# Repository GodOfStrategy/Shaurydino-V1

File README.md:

# Shaurdino-V1
A custom devboard tailored for small and medium applications.
I plan to use it to efficiently reduce electricity consumption in a voice recorder and announcer module of my own.

Key Features
Core MCU:

Raspberry Pi RP2040 dual‑core ARM Cortex‑M0+ processor.

Connected to a 12 MHz crystal oscillator for precise clocking.

USB Interface:

USB‑C connector with ESD protection (USBLC6‑2SC6).

NCP-1117 linear voltage regulator providing a clean 3.3 V rail.

Decoupling capacitors distributed across the board for stable supply.

Designed to accept 5 V from USB or a regulated external source.

Memory:

W25Q32JVSS QSPI flash for program and data storage.

Connected via dedicated QSPI pins for high‑speed access.

Connectivity & Expansion:

Dual 20‑pin headers, exposing GPIO0–GPIO29, ADC inputs, and power rails for running peripherals safely.

Breakout for SWCLK and SWDIO debug signals.

RUN pin with pull‑up for reset control.

Supporting Components:

Crystal oscillator network with capacitors and resistor for stable timing.

Multiple capacitors (C1–C17, C36–C39) for filtering and decoupling higher frequency  and low frequency smoothning.

Resistors for pull‑ups/pull‑downs and configuring certain components.

Here is the 3D model of my PCB.

You can find the schematics in the repository as well as the PCB design and it's Gerber files.
Here are the PCB and Schematics Images for your reference here aswell:

The BOM for the project-

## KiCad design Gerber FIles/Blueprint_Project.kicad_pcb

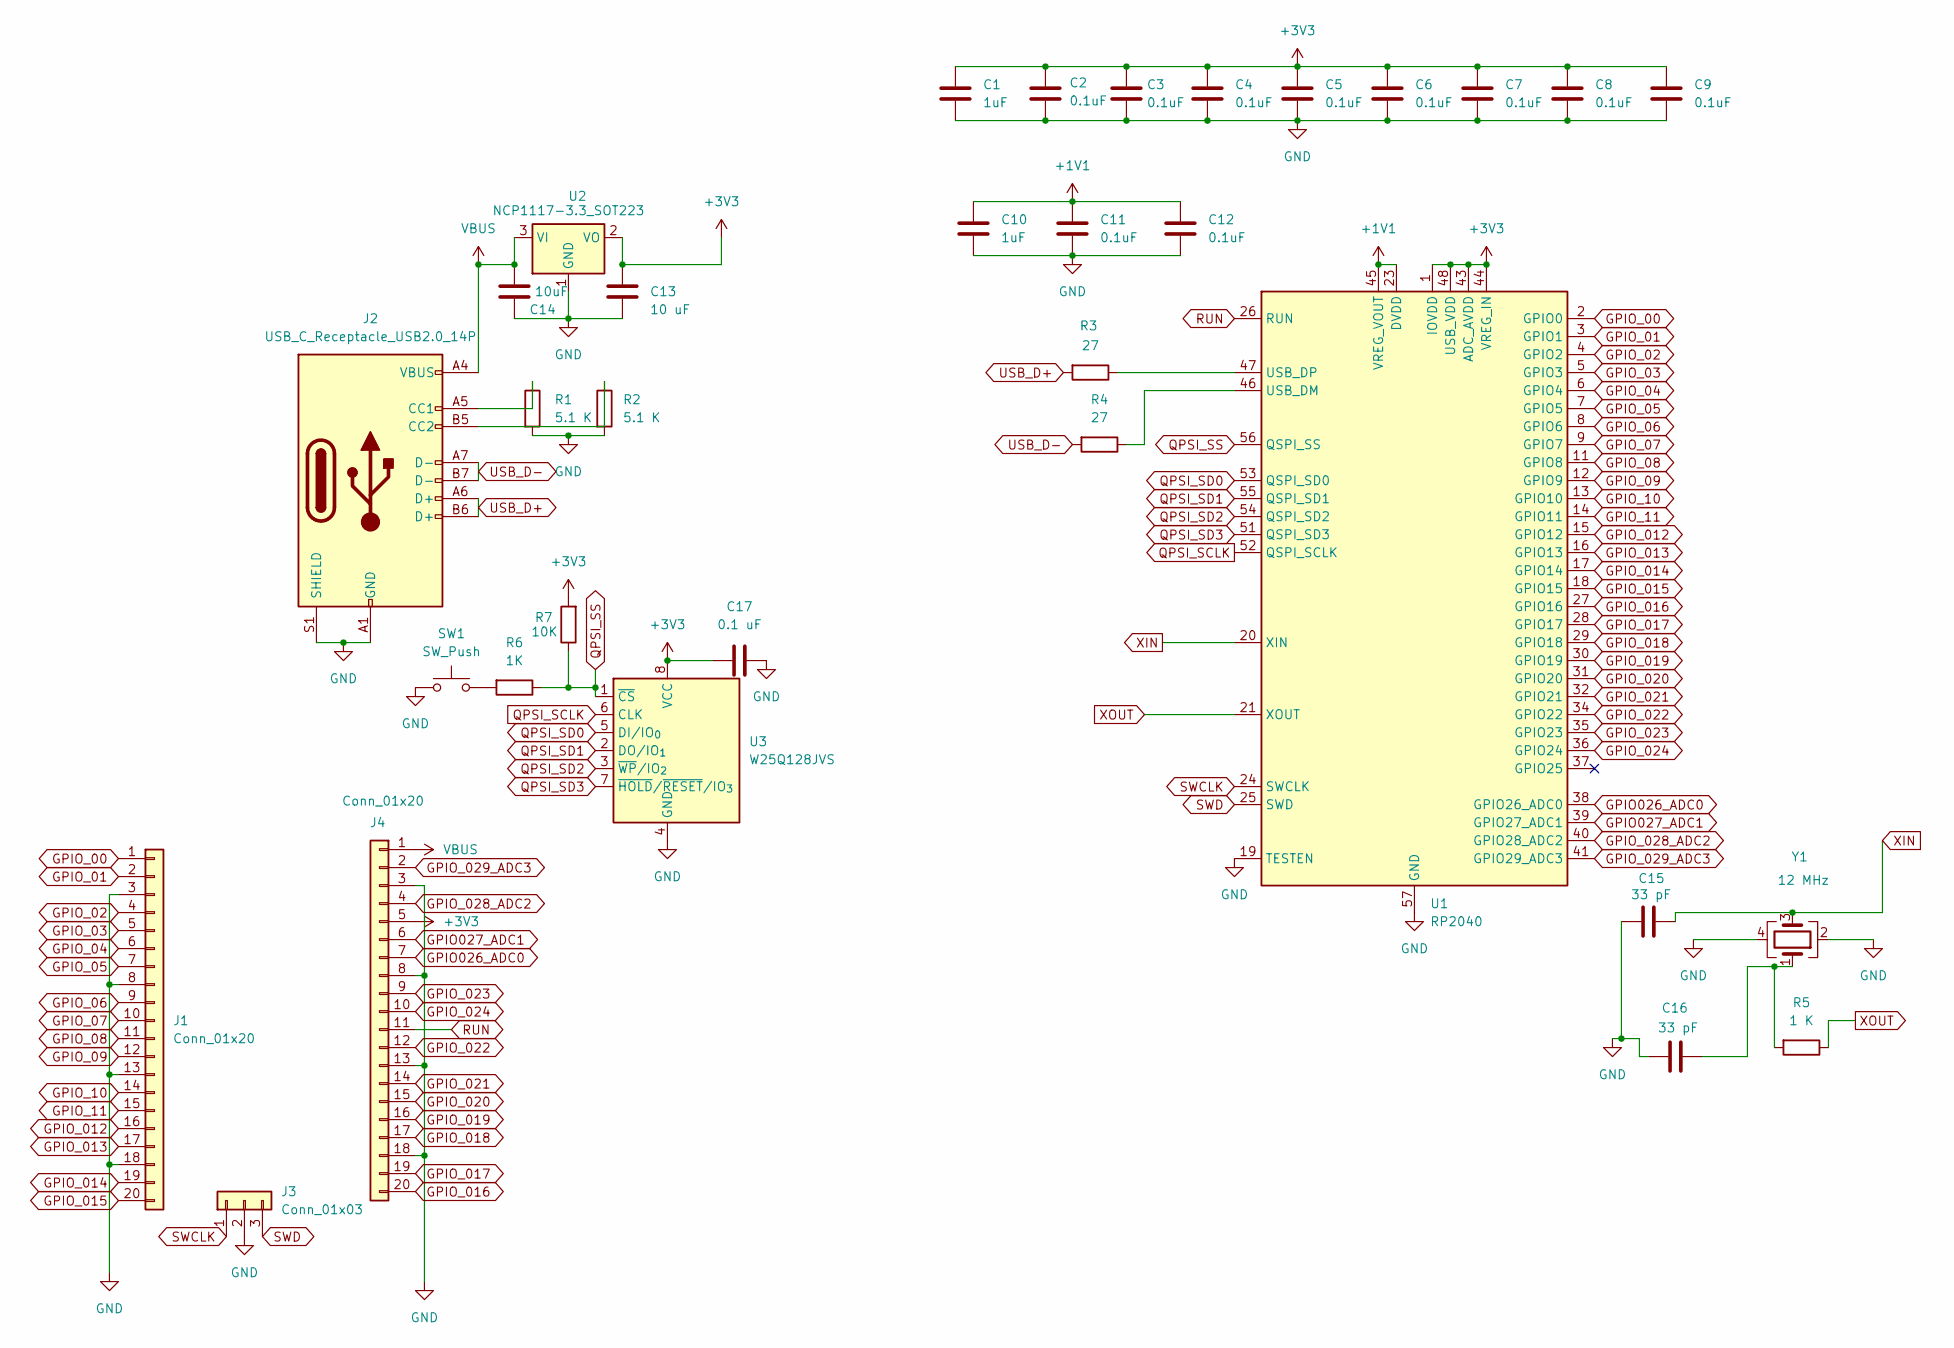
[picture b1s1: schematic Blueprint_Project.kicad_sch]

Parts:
C1, C10: 1uF; C_0402_1005Metric
C2, C3, C4, C5, C6, C7, C8, C9, C11, C12: 0.1uF; C_0402_1005Metric
C13: 10 uF; C_0201_0603Metric
C14: 10uF; C_0201_0603Metric
C15, C16: 33 pF; C_0402_1005Metric
C17: 0.1 uF; C_0402_1005Metric
J1, J4: Conn_01x20; PinHeader_1x20_P2.54mm_Vertical
J2: USB_C_Receptacle_USB2.0_14P; USB_C_Receptacle_HRO_TYPE-C-31-M-12
J3: Conn_01x03; PinHeader_1x03_P2.54mm_Vertical
R1, R2: 5.1 K; R_0402_1005Metric
R3, R4: 27; R_0402_1005Metric
R5: 1 K; R_0402_1005Metric
R6: 1K; R_0402_1005Metric
R7: 10K; R_0402_1005Metric
SW1: SW_Push; SW_Push_SPST_NO_Alps_SKRK
U1: RP2040; QFN-56-1EP_7x7mm_P0.4mm_EP3.2x3.2mm
U2: NCP1117-3.3_SOT223; SOT-223-3_TabPin2
U3: W25Q128JVS; SOIC-8_5.3x5.3mm_P1.27mm
Y1: 12 MHz; Crystal_SMD_3225-4Pin_3.2x2.5mm

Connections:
+1V1: C10.1, C11.1, C12.1, U1.23 (DVDD), U1.45 (VREG_VOUT), U1.50 (DVDD)
+3V3: C1.1, C2.1, C3.1, C4.1, C5.1, C6.1, C7.1, C8.1, C9.1, C13.1, C17.2, J4.5, R7.2, U1.1 (IOVDD), U1.10 (IOVDD), U1.22 (IOVDD), U1.33 (IOVDD), U1.42 (IOVDD), U1.43 (ADC_AVDD), U1.44 (VREG_IN), U1.48 (USB_VDD), U1.49 (IOVDD), U2.2 (VO), U3.8 (VCC)
GND: C1.2, C2.2, C3.2, C4.2, C5.2, C6.2, C7.2, C8.2, C9.2, C10.2, C11.2, C12.2, C13.2, C14.2, C15.2, C16.2, C17.1, J1.3, J1.8, J1.13, J1.18, J2.A1 (GND), J2.A12 (GND), J2.B1 (GND), J2.B12 (GND), J2.S1 (SHIELD), J3.2, J4.3, J4.8, J4.13, J4.18, R1.2, R2.2, SW1.1, U1.19 (TESTEN), U1.57 (GND), U2.1 (GND), U3.4 (GND), Y1.2, Y1.4
GPIO026_ADC0: J4.7, U1.38 (GPIO26_ADC0)
GPIO027_ADC1: J4.6, U1.39 (GPIO27_ADC1)
GPIO_00: J1.1, U1.2 (GPIO0)
GPIO_01: J1.2, U1.3 (GPIO1)
GPIO_02: J1.4, U1.4 (GPIO2)
GPIO_03: J1.5, U1.5 (GPIO3)
GPIO_04: J1.6, U1.6 (GPIO4)
GPIO_05: J1.7, U1.7 (GPIO5)
GPIO_06: J1.9, U1.8 (GPIO6)
GPIO_07: J1.10, U1.9 (GPIO7)
GPIO_08: J1.11, U1.11 (GPIO8)
GPIO_09: J1.12, U1.12 (GPIO9)
GPIO_10: J1.14, U1.13 (GPIO10)
GPIO_11: J1.15, U1.14 (GPIO11)
GPIO_012: J1.16, U1.15 (GPIO12)
GPIO_013: J1.17, U1.16 (GPIO13)
GPIO_014: J1.19, U1.17 (GPIO14)
GPIO_015: J1.20, U1.18 (GPIO15)
GPIO_016: J4.20, U1.27 (GPIO16)
GPIO_017: J4.19, U1.28 (GPIO17)
GPIO_018: J4.17, U1.29 (GPIO18)
GPIO_019: J4.16, U1.30 (GPIO19)
GPIO_020: J4.15, U1.31 (GPIO20)
GPIO_021: J4.14, U1.32 (GPIO21)
GPIO_022: J4.12, U1.34 (GPIO22)
GPIO_023: J4.9, U1.35 (GPIO23)
GPIO_024: J4.10, U1.36 (GPIO24)
GPIO_028_ADC2: J4.4, U1.40 (GPIO28_ADC2)
GPIO_029_ADC3: J4.2, U1.41 (GPIO29_ADC3)
unnamed: C16.1, R5.2, Y1.1
unnamed: J2.A5 (CC1), R1.1
unnamed: J2.B5 (CC2), R2.1
unnamed: R6.2, SW1.2
unnamed: R4.1, U1.46 (USB_DM)
unnamed: R3.1, U1.47 (USB_DP)
QPSI_SCLK: U1.52 (QSPI_SCLK), U3.6 (CLK)
QPSI_SD0: U1.53 (QSPI_SD0), U3.5 (DI/IO_{0})
QPSI_SD1: U1.55 (QSPI_SD1), U3.2 (DO/IO_{1})
QPSI_SD2: U1.54 (QSPI_SD2), U3.3 (~WP/IO_{2})
QPSI_SD3: U1.51 (QSPI_SD3), U3.7 (~HOLD/~RESET/IO_{3})
QPSI_SS: R6.1, R7.1, U1.56 (QSPI_SS), U3.1 (~CS)
RUN: J4.11, U1.26 (RUN)
SWCLK: J3.1, U1.24 (SWCLK)
SWD: J3.3, U1.25 (SWD)
USB_D+: J2.A6 (D+), J2.B6 (D+), R3.2
USB_D-: J2.A7 (D-), J2.B7 (D-), R4.2
VBUS: C14.1, J2.A4 (VBUS), J2.A9 (VBUS), J2.B4 (VBUS), J2.B9 (VBUS), J4.1, U2.3 (VI)
XIN: C15.1, U1.20 (XIN), Y1.3
XOUT: R5.1, U1.21 (XOUT)

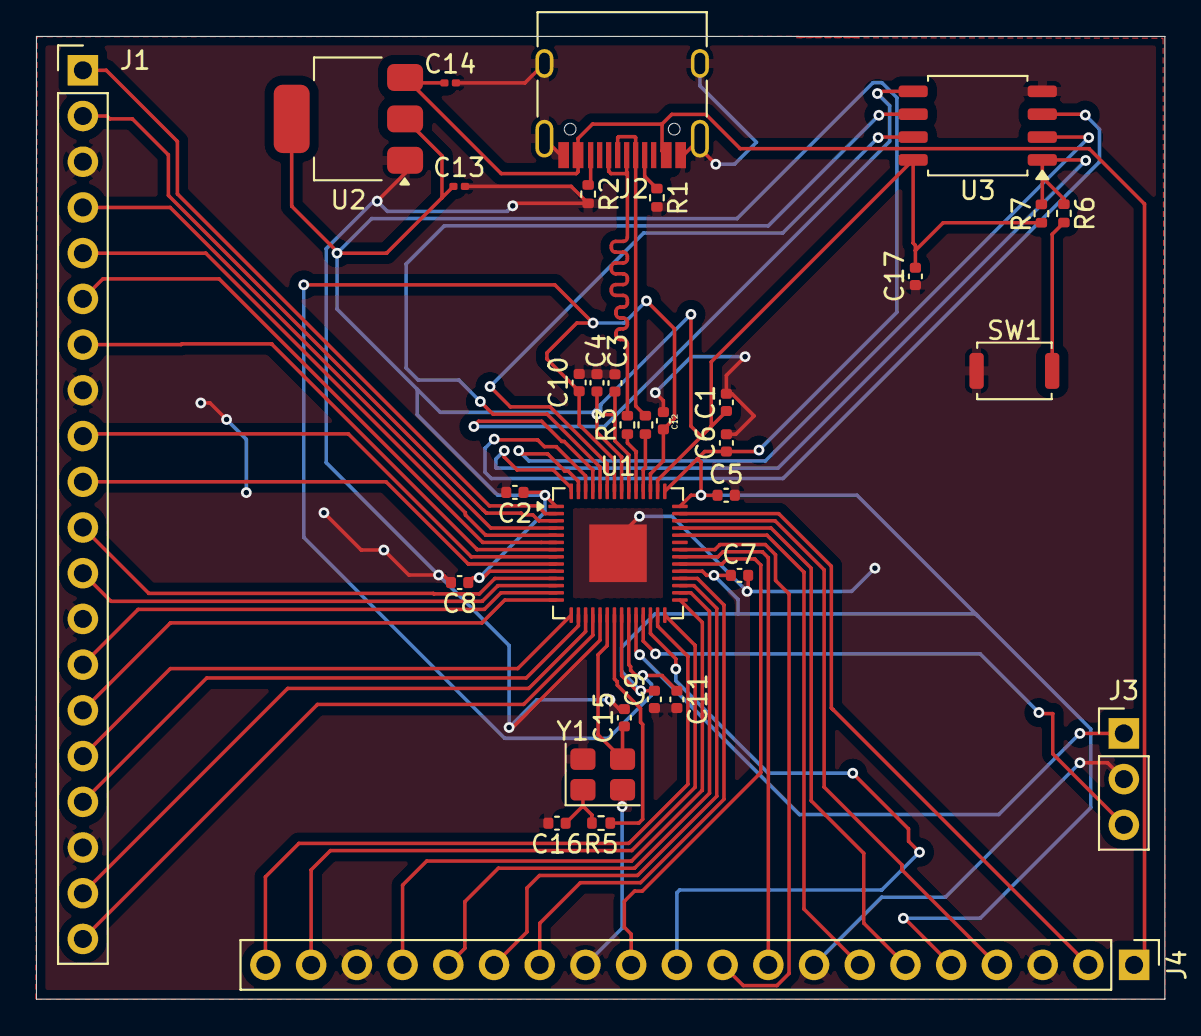
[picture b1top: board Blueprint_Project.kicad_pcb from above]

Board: 2 copper layers, 62.7 x 53.5 mm, 33 parts (0 on the bottom side), 52 nets.

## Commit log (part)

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2025-12-19 ReadMe
    README file for the board
2025-12-19 Update print statement from 'Hello' to 'Goodbye'
2025-12-19 Create Gbr_pcb
2025-12-19 Add gbr_fls.zip to Gbr_pcb
2025-12-19 Create a
2026-01-28 Create Firmware guide
2026-02-17 Update BOM section with additional image
    Added an image to the BOM section and improved formatting.
